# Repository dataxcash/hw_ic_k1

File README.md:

*K1 R2.4-MA full-function production release — 3D top-flat render (4K). Owner-approved
full-function build: all 101 functional devices placed (106 footprints incl. 5
mounting holes), all 90 nets fully routed (0 unconnected), 0 new hard DRC errors
(3 pre-existing J1 Type-C baseline waivers). Auth latch, dual-input power
(12V priority / 5VSB standby) and gated 5V Type-C output are implemented and
firmware-covered (145 host checks). Production board 8142683f (electrically
identical to e744096b; connector 3D models re-aligned, guarded by the rcore
model-alignment gate). Gerbers, drills, POS, BOM and IPC-356 in
`fab/k1_r2_4_fab_20261124/`; differential-pair SI waivers and the 62-item
warning ledger are disclosed in the package as-built notes.*

Open-source hardware — KiCad design files for the **K1 Master Gate Card**,
the master-side converter card in the IOCONVERT V2.0 1-Master-to-4-Worker
chained NTB cluster.

## Overview

K1 sits at the **master side** of a PCIe NTB chain. It provides USB Type-C
management access, pre-authentication gating (SE050 via I2C), and a PCIe
2.1 x2 data path injected into the master host through an OCuLink connector.

```
KEY (secure vault) ──Type-C──► K1 Master Gate Card ──SlimSAS──► Master Host
                                  │
                                  ├─ USB management (SBU I2C ↔ SE050 pre-auth)
                                  ├─ PCIe 2.1 x2 lane injection
                                  └─ 5V pre-auth power rail (TLV61046 boost)
```

## Key Features

- **Form factor**: 70 × 48 mm, 4-layer PCB (#K1-REV-17 缩板)
- **Interface**: USB Type-C (KEY), SlimSAS SFF-8654 4i (host, #W4 换件), 12V DC-in
- **Security**: STM32G0B1 MCU gatekeeper + SE050 pre-authentication via SBU I2C
- **Data path**: PCIe 2.1 x2 with PI3DBS16412 lane-swap MUX
- **Power**: 3.3V_AUX → 5V boost (TLV61046), LDO 5V→3V3, 12V→3V3 DC-DC
- **Management**: OOB UART passthrough, opto-isolated power button (LTV-356T)

## Repository Contents

| Path | Description |
|---|---|
| `k1_v1.kicad_pro` / `.kicad_pcb` | KiCad 10 project + PCB (self-contained) |
| `sch/` | Schematics: top `k1_sch`, connectors, MCU & sideband, power (12V/5V/3V3), input mux & standby, decoupling/redriver VCC + `K1_SCH.kicad_sym` symbol library |
| `lib/ForgeOS.pretty/` | Footprint library (19 footprints) |
| `boards/` | Board/nets configuration (YAML) |
| `fab/` | R2.3 tapeout candidate — KiCad project, PCB, design rules |

## Getting Started

1. Install [KiCad](https://www.kicad.org/) 10.x
2. Clone this repository
3. Open `fab/k1_tapeout_candidate_r2_3_20261122.kicad_pro` (current R2.3
   tapeout candidate) or `k1_v1.kicad_pro` (historical v1 baseline)
4. If symbols/footprints show as missing, add `sch/K1_SCH.kicad_sym`
   to the symbol library table and `lib/ForgeOS.pretty/` to the footprint
   library table (global or project-level)

## Status — 2026-11-22

Tapeout chain: **v1 → R2 → R2.1 → R2.2 → R2.3** (current candidate,
2026-11-22).

- R2.3 board sha256 `553c63bf8573dcd1…`: U1 five-pad schematic-parity ECO
  (pads 2/3/16/23/29 → POWER_LOST_N / AUTH_OK_PULSE / KEY_DET_SENSE /
  MCU_USB_D_N / KEY_PRESENT), restoring the authentication latch clock,
  key-detect sense and USB D-N that were previously grounded or swapped.
  True electrical change: electrical sha `6619987cc47ae7b7…`, track
  segments `0325e382…`, nets 60 → 64 (five nets leave GND and reconnect
  for real); DRC 0 new hard errors, 0 unrouted nets; silkscreen held
  60/60; renders carry full provenance.
- R2.2 board sha256 `a8526b57989c6a89…` (electrical zero-drift vs R2.1,
  geometry sha byte-identical; silkscreen designators re-placed and Value
  fields fixed from truth source); R2.1 sha `74920945c1583fa7…`; DRC at candidate gate: 51 violations =
  0 new hard errors + 3 pre-existing J1 baseline waivers (all soft) + 48 warnings,
  0 unrouted nets; H5 M2.5 NPTH mounting hole added; four connector-family
  orientations solved.
- The R2.3 tapeout candidate (PCB/project/rules) is tracked under `fab/`;
  gerber exports still ship from the working tree at fab hand-off.
- Toolchain migration to the Rust `rcore` engine is underway: milestones
  **M1** (routing: raster/astar/planner/plan_io + model orientation, exact-parity
  vs Python incl. pixel-level Pillow Draw.c reimplementation) and **M2**
  (exam/QA engine, 14-subject exam suite, 479 tests green) are landed;
  **M3** (schematic generation + board tooling) landed.

## License

AGPL-3.0 (see `LICENSE`)

---

*Part of the IOCONVERT V2.0 family: [hw_ic_k2](https://github.com/dataxcash/hw_ic_k2) (worker data-plane card) · [hw_ic_key](https://github.com/dataxcash/hw_ic_key) (secure key vault)*

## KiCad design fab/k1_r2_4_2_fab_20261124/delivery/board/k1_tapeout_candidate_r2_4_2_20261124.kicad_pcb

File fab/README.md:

# `k1/fab/` —— 制造输入件（K1 项目面）

## 当前生产口径（2026-11-24）

- 现行生产板：`fab/k1_tapeout_candidate_r2_4_2_20261124.kicad_pcb`
  - sha256 `a4719b536a81d42ea346f87207fb5af7ccaa3b1cd20c39c2a58295a0d45eaf8f`
  - 电气指纹 `9efd27734c8adced249b5356155ab58bfc6c9e8902e025bcb9cb90a1016d12ad`；track `6b1a25d537ff8bebfbdd9ada7b7e476c1ae1c25d59d9b17d3de416945e086751`（与 R2.4-MA `8142683f` 电气零变；仅 F.SilkS 位号字号/线宽整体降一号）
  - 源 ALT `a4719b53…` 字节级副本；SPEC 2.1 同行，`production_release.board_sha256 = a4719b53…`
- 生产包：`fab/k1_r2_4_2_fab_20261124/`（验收/落盘证据见目录内 `LANDING_MANIFEST.json` / `LANDING_VERIFICATION.txt`）
- 历史：`fab/k1_r2_4_fab_20261124/`（R2.4-MA `8142683f`）标 **SUPERSEDED**，只读保留；旧扁平件 `k1_tapeout_candidate_r2_4_ma_20261124.*` 已 `git rm`（历史在 git）
- 授权：`msg-20261124-105501-k1-mcp-report` / 判决 `K1-R242FAB-ACCEPT-20261124`
- DRC 口径：R2.4.2 `109 = 3` 既有 J1 error + `106` warning，`unconnected=0`；`text_height` 15→61 系 owner 指定字号降档可预期告警，无新增硬错误
- 厂商下单第三项确认：丝印最小线宽 `0.1mm`、极限字高 `0.65×49` / `0.25×1` 可产性

| 件 | sha256(16) | 口径 / 用途 | 生成器 |
|---|---|---|---|
| `k1_v1_bom.csv` | `2b7b2554f835689e` | **ref 集 BOM**（`Ref` 头 + **每行一 ref**，**37 refs**）：满足 `_shared/eda_core/pipeline/checks.py::check_bom_consistent` 的消费口径（`row[0].split(",")`），是 `k1/pipeline.yaml` 安装的**具名前置**（#K2-49 §二 M3 前置） | `k1/tools/k1_p4_bom_gen_v1.py`（K2 同构移植） |

## 口径说明（勿误用）

- **「每行一 ref」是正确性前提，不是风格**：`check_bom_consistent` 逐行 `csv.reader(row)[0].split(",")` ⇒ 未加引号的多 ref 同行会被拆列、只读到第一个 ⇒ 误报「BOM 与 sch 不同步」（K2 侧 inc58 §0-5 / inc63 §0-3 负控已证）。
- **来源 = 真 sch netlist**（`kicad-cli sch export netlist --format kicadsexpr`，经 `$SHARUN`），**不读板 / 不读 SPEC**（避 C-1）；并与真源 `pm_gate/project.yaml::nets_yaml`（= `boards/k1_sch.yaml`）placements **交叉核对**（37 == 37），不一致即 fail-closed。
- **本件只是「判据消费口径」的 ref 集**；含 `Value`/`Footprint`/`Qty`/`LCSC` 的**交付级 BOM 属 P5 交付面**（另件另裁）——**勿把本件当交付 BOM**。
- ⚠ **须随原理图变更同步**：N-3（K1 原理图再生 37→42）落件后，本件 ref 集会与 sch netlist 不一致 ⇒ `bom_consistent` 将 FAIL ⇒ **须以本生成器重出并同批提交**。

生成（dry-run 只打印/校验；写仓库须双闸）：

```bash
cd /home/fila/jqdDev_2025/ic_hw
python3 k1/tools/k1_p4_bom_gen_v1.py                                  # dry-run（打印 + 交叉核对 + 预测 sha）
python3 k1/tools/k1_p4_bom_gen_v1.py --apply --confirm-repo-write     # 落本目录（T-41/T-22：落盘前自动备份并打印旧 sha）
```

授权：#K2-49 §三-2（BOM 落件 → M3 同批）。

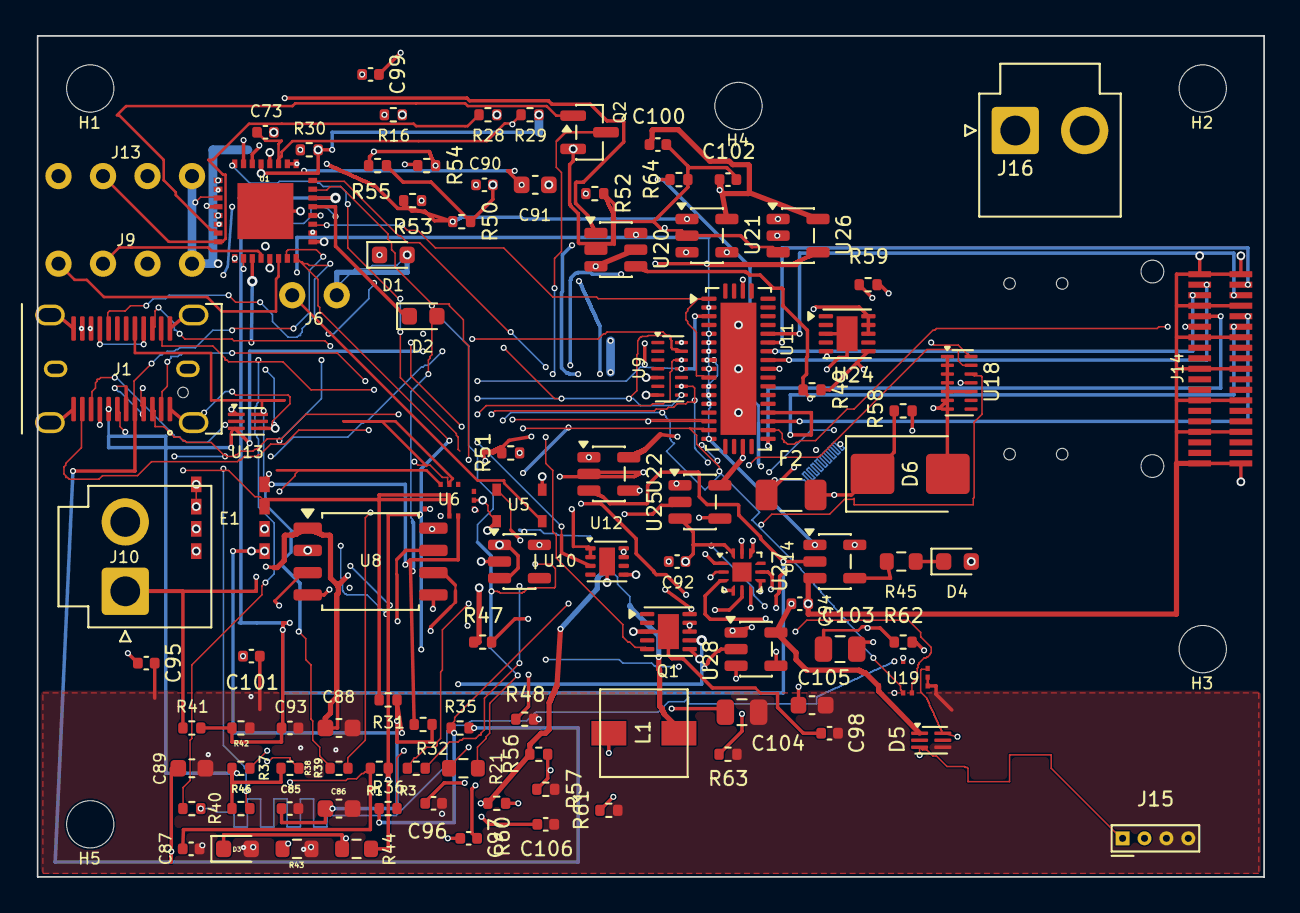
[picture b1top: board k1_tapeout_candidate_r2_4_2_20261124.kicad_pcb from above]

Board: 4 copper layers, 70.0 x 48.0 mm, 106 parts (0 on the bottom side), 87 nets.

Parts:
C73, C85, C87, C90, C92, C93, C94, C97, C98, C99, C100, C101, C102, C106: 100nF; C_0402_1005Metric
C86, C89: 4.7uF; C_0603_1608Metric
C88, C91, C105: 1uF; C_0603_1608Metric
C95: 1uF; C_0402_1005Metric
C96: 6.8nF; C_0402_1005Metric
C103, C104: 10uF; C_0805_2012Metric
D1, D2, D3, D4: LED; LED_0603_1608Metric
D5: TPD2E001; DFN-6_1.6x1.3mm_P0.4mm
D6: SMBJ5.0A; D_SMB
E1: FRU EEPROM; SOIC8_FRU
F2: FUSE_3A; Fuse_1206_3216Metric
H1, H2, H3, H4, H5: MountingHole M2.5 NPTH; MountingHole_M2.5_NPTH
J1: USB Type-C JAE DX07S024WJ1R350; USB_C_Receptacle_JAE_DX07S024WJ1R350
J6: PinHeader 1x02; PinHeader_1x02
J9, J13: PinHeader 1x04; PinHeader_1x04
J10: JST VH B2P-VH; JST_VH_B2P-VH_1x02_P3.96mm_Vertical
J14: SlimSAS SFF-8654 38pin; SlimSAS_4x_SFF-8654_38pin_RASide
J15: HOST_USB2_4P; PinHeader_1x04_P1.25mm_Vertical
J16: JST_VH_B2P-VH; JST_VH_B2P-VH_1x02_P3.96mm_Vertical
L1: 3.3uH; L_3.3uH_5.0x5.0mm
Q1: TPS22990; WSON-10-1EP_2.5x2.5mm_P0.5mm_EP1.2x2mm
Q2: 2N7002; SOT-23
R1, R16, R28, R29, R35, R36, R37, R56, R58: 10K; R_0402_1005Metric
R3: 220R; R_0402_1005Metric
R21, R43, R44, R45: 1K; R_0603_1608Metric
R30: 0R; R_0402_1005Metric
R31, R32: 4.7k; R_0402_1005Metric
R38, R39: 22R; R_0402_1005Metric
R40: 100R; R_0402_1005Metric
R41, R46, R49, R50, R51, R54, R57, R60, R62: 100K; R_0402_1005Metric
R42, R59, R64: 33K; R_0402_1005Metric
R47: 124K; R_0402_1005Metric
R48: 22.1K; R_0402_1005Metric
R52, R55: 56K; R_0402_1005Metric
R53: 1M; R_0402_1005Metric
R61, R63: 22K1; R_0402_1005Metric
U1: STM32G0B1KBU6N; MCU_STM32G0_QFN32
U5: LTV-356T; OPTO_LTV356T
U6, U19: TS3USB221A; TS3USB221A_UQFN10
U8: TPS54628; SOIC-8_5.3x5.3mm_P1.27mm
U9, U18: TPD6E05U06; TPD6E05U06_RVZ
U10: LDO 5V-3V3; SOT-23-5
U11: PI3DBS16412
U12: TPS22965; Texas_DSG0008A_WSON-8-1EP_2x2mm_P0.5mm_EP0.9x1.6mm
U13: TPD2E001; DFN-6_1.6x1.3mm_P0.4mm
U14, U25, U28: 74LVC1G08; SOT-23-5
U20: SN74LVC1G175; SOT-23-6
U21, U22: TLV7011; SOT-23-5
U24: TPS22990; WSON-10-1EP_2.5x2.5mm_P0.5mm_EP1.2x2mm
U26: 74LVC1G00; SOT-23-5
U27: TPS2121; IDT_QFN-12-1EP_2x2mm_P0.5mm_EP1.1x1.1mm

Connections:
5VSB_IN: F2.1, J16.1
5VSB_PROT: C103.1, D6.1, F2.2, R58.1, R62.1, U27.2
12V_IN: C88.1, J10.1, R41.1, U8.1, U8.8
AUTHORIZED: R49.1, U19.9, U20.4, U28.1
AUTH_CLR_N: U20.6, U25.4
AUTH_LED: D2.1, U1.12
AUTH_LED_K: D2.2, R43.1
AUTH_OK_PULSE: U1.3, U20.1
CC1: J1.A5, R35.2, U1.18
CC2: J1.B5, R36.2, U1.17
D_P_HOLD: R40.1, U1.22
GND: C73.2, C85.2, C86.2, C87.2, C88.2, C89.2, C90.2, C91.2, C92.2, C93.2, C94.2, C95.2, C96.2, C98.2, C99.2, C100.2, C101.2, C102.2, C103.2, C104.2, C105.2, C106.2, D1.2, D3.2, D4.2, D5.4, D6.2, E1.1, E1.2, E1.3, E1.4, E1.7, J1.A1, J1.A12, J1.B1, J1.B12, J1.SH, J6.2, J9.3, J10.2, J13.3, J14.A1, J14.A4, J14.A7, J14.A10, J14.A13, J14.A16, J14.A19, J14.B1, J14.B4, J14.B7, J14.B10, J14.B13, J14.B16, J14.B19, J15.3, J15.4, J16.2, Q1.6, Q2.2, R16.2, R28.2, R42.2, R43.2, R48.2, R49.2, R50.2, R52.2, R55.2, R57.2, R59.2, R61.2, R63.2, R64.2, U1.5, U1.33, U5.2, U5.3, U6.5, U8.5, U9.5, U9.7, U10.2, U11.CP, U12.5, U12.9, U13.4, U14.3, U18.1, U18.2, U18.3, U18.4, U18.5, U18.6, U18.7, U18.10, U19.5, U19.6, U20.2, U21.2, U22.2, U24.6, U25.3, U26.3, U27.12, U28.3
GPIO_LED: R21.1, U1.15
HOST_PWR_DET: C93.1, R41.2, R42.1, U1.11, U14.2, U22.3
HOST_USB2_D_N: D5.6, J15.2, U19.4
HOST_USB2_D_P: D5.3, J15.1, U19.3
I2C1_SCL: E1.6, R31.1, U1.30, U6.8
I2C1_SDA: E1.5, R32.1, U1.31, U6.7
J14_RX0_N: J14.A2, U11.31
J14_RX0_P: J14.A3, U11.32
J14_RX1_N: J14.A5, U11.22
J14_RX1_P: J14.A6, U11.23
J14_TX0_N: J14.B2, U11.33
J14_TX0_P: J14.B3, U11.34
J14_TX1_N: J14.B5, U11.24
J14_TX1_P: J14.B6, U11.25
KEY_DET_EN: Q2.1, U1.26
KEY_DET_REF: R51.2, R52.1, U21.4
KEY_DET_RET: Q2.3, R37.2
KEY_DET_SENSE: R46.2, R53.2, U1.16, U21.3
KEY_D_N: J1.A7, U9.13, U19.7
KEY_D_P: J1.A6, U9.14, U19.8
KEY_PRESENT: R50.1, R53.1, U1.29, U21.1, U25.1, U26.2
LED_A: D1.1, R21.2
MCU_USB_D_N: U1.23, U19.2
MCU_USB_D_P: R40.2, U19.1
MCU_VDD: C85.1, C86.1, E1.8, J9.4, J13.4, R29.2, R30.2, R31.2, R32.2, U1.4, U1.20
MUX_PD: U1.14, U11.1, U11.10
MUX_SEL: U1.28, U11.8, U11.17, U14.1
NRST: C73.1, R29.1, U1.6, U25.2
P3V3_AUX: C90.1, C91.1, C94.1, C100.1, C101.1, C102.1, D5.1, R1.2, R30.1, R44.2, R51.1, R54.1, U1.13, U6.10, U10.5, U11.5, U11.9, U11.13, U11.20, U11.30, U11.40, U13.1, U14.5, U19.10, U20.3, U20.5, U21.5, U22.5, U25.5, U26.5, U28.5
PCIE_GATE: R45.1, U14.4
PCIE_LED_K: D4.1, R45.2
PCIE_RX0_N: J1.A10, U9.8, U11.7
PCIE_RX0_P: J1.A11, U9.9, U11.6
PCIE_RX1_N: J1.B10, U11.16, U18.11
PCIE_RX1_P: J1.B11, U11.15, U18.12
PCIE_TX0_N: J1.A2, U9.11, U11.3
PCIE_TX0_P: J1.A3, U9.12, U11.2
PCIE_TX1_N: J1.B2, U11.12, U18.13
PCIE_TX1_P: J1.B3, U11.11, U18.14
PERSTA#: C87.1, R1.1, U1.7, U1.8
POWER_LOST_N: U1.2, U22.1, U28.2
PWR_5V_FB: R47.2, R48.1, U8.2
PWR_5V_MAIN: C89.1, L1.2, R47.1, R56.1, R60.1, U27.7
PWR_5V_SS: C96.1, U8.4
PWR_5V_SW: C97.2, L1.1, U8.6
PWR_5V_SYS: C104.1, C106.1, U10.1, U10.3, U12.1, U12.2, U24.3, U24.11, U27.1, U27.8
PWR_5V_VBST: C97.1, U8.7
PWR_5V_VREG5: C95.1, U8.3
PWR_5V_WORK: C98.1, Q1.3, Q1.11, U24.8, U24.9, U24.10
PWR_BTN_ISO: R3.2, U5.1
PWR_BTN_OUT: R3.1, U1.10
PWR_CTRL_OUT: J6.1, U5.4
PWR_FAIL_REF: C99.1, R54.2, R55.1, U22.4
PWR_MUX_CP2: R58.2, R59.1, U27.3
PWR_MUX_ILIM: R64.1, U27.10
PWR_MUX_OV1: R60.2, R61.1, U27.5
PWR_MUX_OV2: R62.2, R63.1, U27.4
PWR_MUX_PR1: R56.2, R57.1, U27.6
PWR_MUX_SS: C105.1, U27.11
SBU1: J1.A8, R37.1, R38.1, R46.1, U13.3
SBU1_INT: R38.2, U6.1
SBU2: J1.B8, R39.1, U13.6
SBU2_INT: R39.2, U6.2
SBU_EN: U1.1, U26.1
SBU_SEL: R16.1, U1.32, U6.9
SWCLK_BOOT0: J13.2, R28.1, U1.25
SWDIO: J13.1, U1.24
TPS_EN: U1.27, U12.3
U6_OE_N: U6.6, U26.4
UART_RX: J9.2, U1.21
UART_TX: J9.1, U1.19
VBUS: C92.1, J1.A4, J1.A9, J1.B4, J1.B9, Q1.8, Q1.9, Q1.10, R35.1, R36.1, U12.7, U12.8
WORK_EN: Q1.5, U1.9
WORK_PG: D3.1, Q1.7, R44.1
WORK_RAIL_EN: U24.5, U28.4

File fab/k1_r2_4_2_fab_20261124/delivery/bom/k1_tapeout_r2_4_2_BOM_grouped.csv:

Value,Footprint,Lib,Population,Process,Qty,Refs,Description
0R,R_0402_1005Metric,Resistor_SMD,PLACE,SMT,1,R30,
100K,R_0402_1005Metric,Resistor_SMD,PLACE,SMT,9,R41 R46 R49 R50 R51 R54 R57 R60 R62,
100nF,C_0402_1005Metric,Capacitor_SMD,PLACE,SMT,14,C73 C85 C87 C90 C92 C93 C94 C97 C98 C99 C100 C101 C102 C106,
100R,R_0402_1005Metric,Resistor_SMD,PLACE,SMT,1,R40,
10K,R_0402_1005Metric,Resistor_SMD,PLACE,SMT,9,R1 R16 R28 R29 R35 R36 R37 R56 R58,
10uF,C_0805_2012Metric,Capacitor_SMD,PLACE,SMT,2,C103 C104,
124K,R_0402_1005Metric,Resistor_SMD,PLACE,SMT,1,R47,
1K,R_0603_1608Metric,Resistor_SMD,PLACE,SMT,4,R21 R43 R44 R45,
1M,R_0402_1005Metric,Resistor_SMD,PLACE,SMT,1,R53,
1uF,C_0402_1005Metric,Capacitor_SMD,PLACE,SMT,1,C95,
1uF,C_0603_1608Metric,Capacitor_SMD,PLACE,SMT,3,C88 C91 C105,
22.1K,R_0402_1005Metric,Resistor_SMD,PLACE,SMT,1,R48,
220R,R_0402_1005Metric,Resistor_SMD,PLACE,SMT,1,R3,
22K1,R_0402_1005Metric,Resistor_SMD,PLACE,SMT,2,R61 R63,
22R,R_0402_1005Metric,Resistor_SMD,PLACE,SMT,2,R38 R39,
2N7002,SOT-23,Package_TO_SOT_SMD,PLACE,SMT,1,Q2,
3.3uH,L_3.3uH_5.0x5.0mm,ForgeOS,PLACE,SMT,1,L1,
33K,R_0402_1005Metric,Resistor_SMD,PLACE,SMT,3,R42 R59 R64,
4.7k,R_0402_1005Metric,Resistor_SMD,PLACE,SMT,2,R31 R32,
4.7uF,C_0603_1608Metric,Capacitor_SMD,PLACE,SMT,2,C86 C89,
56K,R_0402_1005Metric,Resistor_SMD,PLACE,SMT,2,R52 R55,
6.8nF,C_0402_1005Metric,Capacitor_SMD,PLACE,SMT,1,C96,
74LVC1G00,SOT-23-5,Package_TO_SOT_SMD,PLACE,SMT,1,U26,
74LVC1G08,SOT-23-5,Package_TO_SOT_SMD,PLACE,SMT,3,U14 U25 U28,
FRU EEPROM,SOIC8_FRU,ForgeOS,PLACE,SMT,1,E1,
FUSE_3A,Fuse_1206_3216Metric,Fuse,PLACE,SMT,1,F2,
HOST_USB2_4P,PinHeader_1x04_P1.25mm_Vertical,ForgeOS,PLACE,THT,1,J15,
JST VH B2P-VH,JST_VH_B2P-VH_1x02_P3.96mm_Vertical,Connector_JST,PLACE,THT,1,J10,
JST_VH_B2P-VH,JST_VH_B2P-VH_1x02_P3.96mm_Vertical,Connector_JST,PLACE,THT,1,J16,
LDO 5V-3V3,SOT-23-5,Package_TO_SOT_SMD,PLACE,SMT,1,U10,
LED,LED_0603_1608Metric,LED_SMD,PLACE,SMT,4,D1 D2 D3 D4,
LTV-356T,OPTO_LTV356T,ForgeOS,PLACE,SMT,1,U5,
MountingHole M2.5 NPTH,MountingHole_M2.5_NPTH,ForgeOS,NO_PLACE_NPTH_MECHANICAL,NPTH_MECHANICAL,5,H1 H2 H3 H4 H5,
PI3DBS16412,PI3DBS16412,ForgeOS,PLACE,SMT,1,U11,
PinHeader 1x02,PinHeader_1x02,ForgeOS,PLACE,THT,1,J6,
PinHeader 1x04,PinHeader_1x04,ForgeOS,PLACE,THT,2,J9 J13,
SlimSAS SFF-8654 38pin,SlimSAS_4x_SFF-8654_38pin_RASide,ForgeOS,PLACE,SMT,1,J14,
SMBJ5.0A,D_SMB,Diode_SMD,PLACE,SMT,1,D6,
SN74LVC1G175,SOT-23-6,Package_TO_SOT_SMD,PLACE,SMT,1,U20,
STM32G0B1KBU6N,MCU_STM32G0_QFN32,ForgeOS,PLACE,SMT,1,U1,STM32G0B1KBU6N UFQFPN32 5x5mm; KBU6/KBU6N package-compatible; pin17=PB15/UCPD1_CC2
TLV7011,SOT-23-5,Package_TO_SOT_SMD,PLACE,SMT,2,U21 U22,
TPD2E001,DFN-6_1.6x1.3mm_P0.4mm,Package_DFN_QFN,PLACE,SMT,2,D5 U13,
TPD6E05U06,TPD6E05U06_RVZ,ForgeOS,PLACE,SMT,2,U9 U18,
TPS2121,IDT_QFN-12-1EP_2x2mm_P0.5mm_EP1.1x1.1mm,Package_DFN_QFN,PLACE,SMT,1,U27,
TPS22965,Texas_DSG0008A_WSON-8-1EP_2x2mm_P0.5mm_EP0.9x1.6mm,Package_SON,PLACE,SMT,1,U12,
TPS22990,WSON-10-1EP_2.5x2.5mm_P0.5mm_EP1.2x2mm,Package_SON,PLACE,SMT,2,Q1 U24,
TPS54628,SOIC-8_5.3x5.3mm_P1.27mm,Package_SO,PLACE,SMT,1,U8,
TS3USB221A,TS3USB221A_UQFN10,ForgeOS,PLACE,SMT,2,U6 U19,
USB Type-C JAE DX07S024WJ1R350,USB_C_Receptacle_JAE_DX07S024WJ1R350,ForgeOS,PLACE,MIXED_SMD_PTH,1,J1,

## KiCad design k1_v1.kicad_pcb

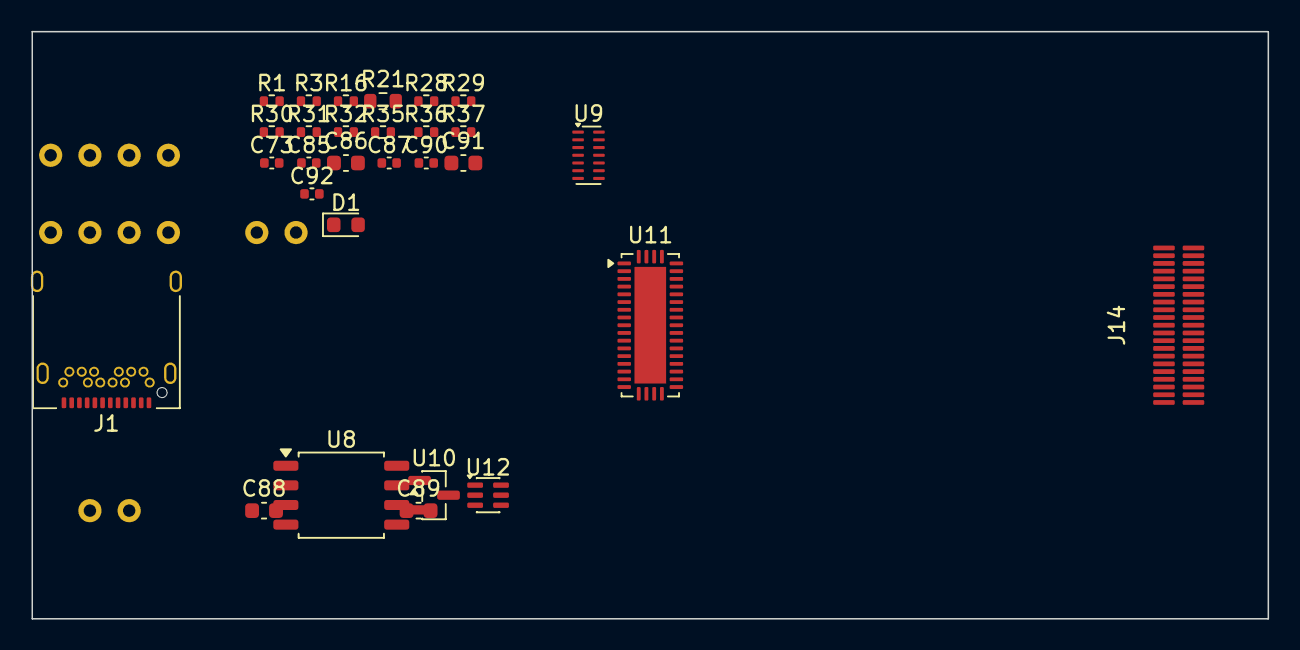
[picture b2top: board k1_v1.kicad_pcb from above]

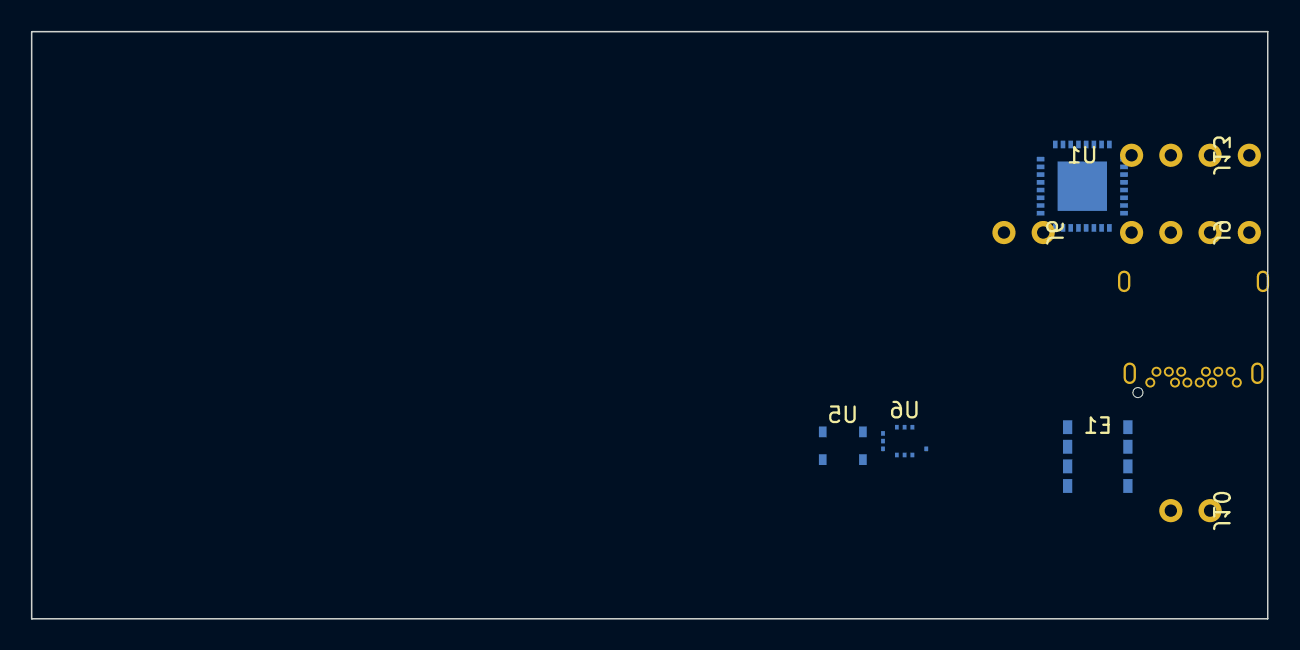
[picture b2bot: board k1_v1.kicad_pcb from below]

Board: 4 copper layers, 80.0 x 38.0 mm, 37 parts (8 on the bottom side), 47 nets, no tracks yet.

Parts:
C73, C85, C87, C90, C92: C_0402_1005Metric
C86, C88, C89, C91: C_0603_1608Metric
D1: LED_0603_1608Metric
E1: SOIC8_FRU
J1: USB_C_Receptacle_Amphenol_12401548E4-2A
J6, J10: PinHeader_1x02
J9, J13: PinHeader_1x04
J14: OCuLink_SFF8612
R1, R3, R16, R28, R29, R30, R31, R32, R35, R36, R37: R_0402_1005Metric
R21: R_0603_1608Metric
U1: MCU_STM32G0_QFN32
U5: OPTO_LTV356T
U6: TS3USB221A_UQFN10
U8: SOIC-8_5.3x5.3mm_P1.27mm
U9: TPD6E05U06_RVZ
U10: SOT-23
U11: PI3DBS16412
U12: TPS22919

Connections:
12V_IN: C88.1, J10.1, U8.4, U8.6
CC1: J1.A5, R35.2
CC2: J1.B5, R36.2
GND: C73.2, C85.2, C86.2, C87.2, C88.2, C89.2, C90.2, C91.2, C92.2, D1.2, E1.1, E1.4, J1.A1, J1.A12, J1.B1, J1.B12, J6.2, J10.2, J14.A2, J14.A5, J14.A8, J14.A11, J14.A13, J14.A14, J14.A17, J14.A20, J14.B2, J14.B5, J14.B8, J14.B11, J14.B14, J14.B17, J14.B20, R16.2, R28.2, R37.2, U1.8, U1.22, U1.32, U5.4, U6.1, U8.2, U9.13, U9.14, U11.4, U11.14, U11.19, U11.21, U11.39, U11.41, U11.CP, U12.2
GPIO_LED: R21.1, U1.24
I2C1_SCL: E1.5, R31.1, U1.11, U6.2
I2C1_SDA: E1.6, R32.1, U1.12, U6.3
KEY_D_N: J1.A7, U9.2
KEY_D_P: J1.A6, U9.1
LED_A: D1.1, R21.2
MCU_VDD: C85.1, C86.1, E1.8, R29.2, R30.2, R31.2, R32.2, U1.21
MUX_PD: U1.14, U11.1, U11.10
MUX_SEL: U1.15, U11.8, U11.17
NC: U11.18, U11.42
NRST: C73.1, R29.1, U1.1
OCuLink_RX0_N: J14.B4, U11.31
OCuLink_RX0_P: J14.B3, U11.32
OCuLink_RX1_N: J14.B7, U11.22
OCuLink_RX1_P: J14.B6, U11.23
OCuLink_TX0_N: J14.A4, U11.33
OCuLink_TX0_P: J14.A3, U11.34
OCuLink_TX1_N: J14.A7, U11.24
OCuLink_TX1_P: J14.A6, U11.25
P3V3_AUX: C90.1, C91.1, R1.2, R30.1, U1.7, U6.10, U11.5, U11.9, U11.13, U11.20, U11.30, U11.40
PCIE_RX0_N: J1.B10, U9.6, U11.7
PCIE_RX0_P: J1.B11, U9.5, U11.6
PCIE_RX1_N: J1.A10, U11.16
PCIE_RX1_P: J1.A11, U11.15
PCIE_TX0_N: J1.A2, U9.4, U11.3
PCIE_TX0_P: J1.A3, U9.3, U11.2
PCIE_TX1_N: J1.B2, U11.12
PCIE_TX1_P: J1.B3, U11.11
PERSTA#: C87.1, R1.1, U1.4
PWR_5V_KEY: C89.1, U8.5, U12.1
PWR_5V_PREAUTH: C92.1, J1.A4, J1.A9, J1.B4, J1.B9, R35.1, R36.1, U12.6
PWR_BTN_ISO: R3.2, U5.1, U5.2
PWR_BTN_OUT: R3.1, U1.23
PWR_CTRL_OUT: J6.1, U5.3
SBU1: J1.A8, R37.1, U1.17, U6.4
SBU2: J1.B8, U6.5
SBU_EN: U1.31, U6.9
SBU_SEL: R16.1, U1.6, U6.8
SWCLK_BOOT0: J13.1, R28.1, U1.20
SWDIO: J13.2, U1.19
TPS_EN: U1.26, U12.3
UART_RX: J9.2, U1.18
UART_TX: J9.1, U1.13
